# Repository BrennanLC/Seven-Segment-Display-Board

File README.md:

# Seven-Segment-Display-Board
This is a kicad design project for a seven segment display board

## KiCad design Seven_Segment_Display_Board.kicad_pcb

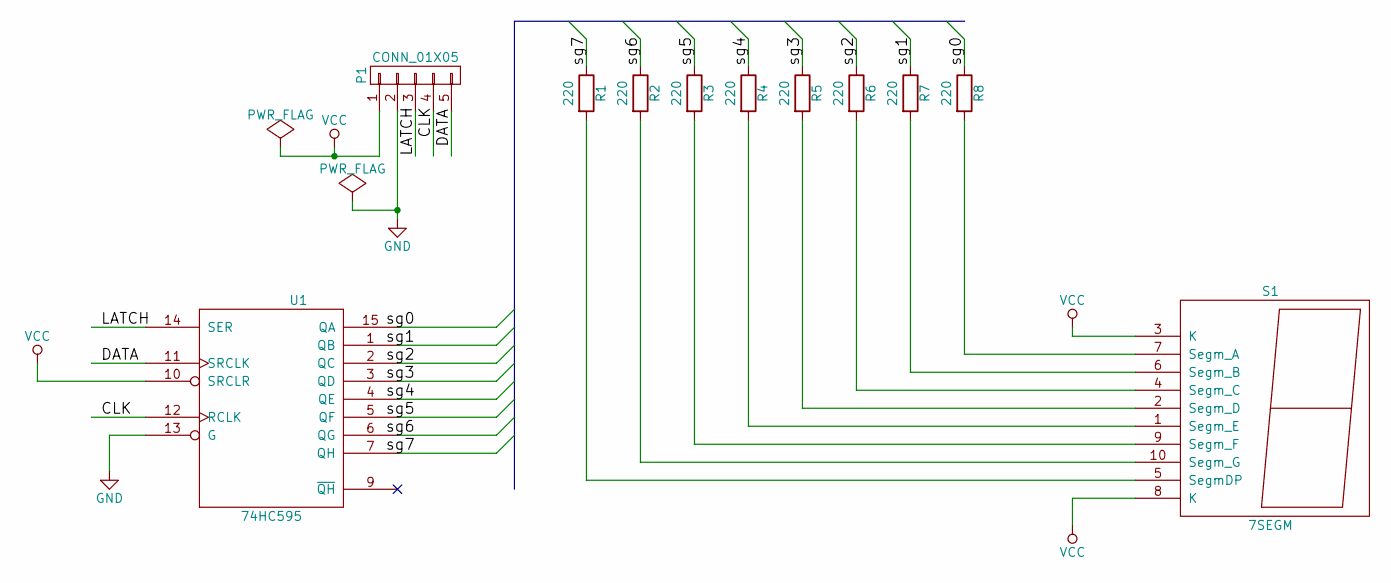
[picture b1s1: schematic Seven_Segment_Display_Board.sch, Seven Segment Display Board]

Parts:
P1: CONN_01X05; Pin_Header_Straight_1x05
R1, R2, R3, R4, R5, R6, R7, R8: 220; Resistor_Horizontal_RM10mm
S1: 7SEGM; 7SegmentLED_LTS6760_LTS6780
U1: 74HC595; DIP-16_W7.62mm

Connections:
/CLK: P1.4, U1.12 (RCLK)
/DATA: P1.5, U1.11 (SRCLK)
/LATCH: P1.3, U1.14 (SER)
/sg0: R8.1, U1.15 (QA)
/sg1: R7.1, U1.1 (QB)
/sg2: R6.1, U1.2 (QC)
/sg3: R5.1, U1.3 (QD)
/sg4: R4.1, U1.4 (QE)
/sg5: R3.1, U1.5 (QF)
/sg6: R2.1, U1.6 (QG)
/sg7: R1.1, U1.7 (QH)
GND: P1.2, U1.8 (GND), U1.13 (G)
unnamed: R1.2, S1.5 (SegmDP)
unnamed: R2.2, S1.10 (Segm_G)
unnamed: R3.2, S1.9 (Segm_F)
unnamed: R4.2, S1.1 (Segm_E)
unnamed: R5.2, S1.2 (Segm_D)
unnamed: R6.2, S1.4 (Segm_C)
unnamed: R7.2, S1.6 (Segm_B)
unnamed: R8.2, S1.7 (Segm_A)
VCC: P1.1, S1.3 (K), S1.8 (K), U1.10 (SRCLR), U1.16 (VCC)

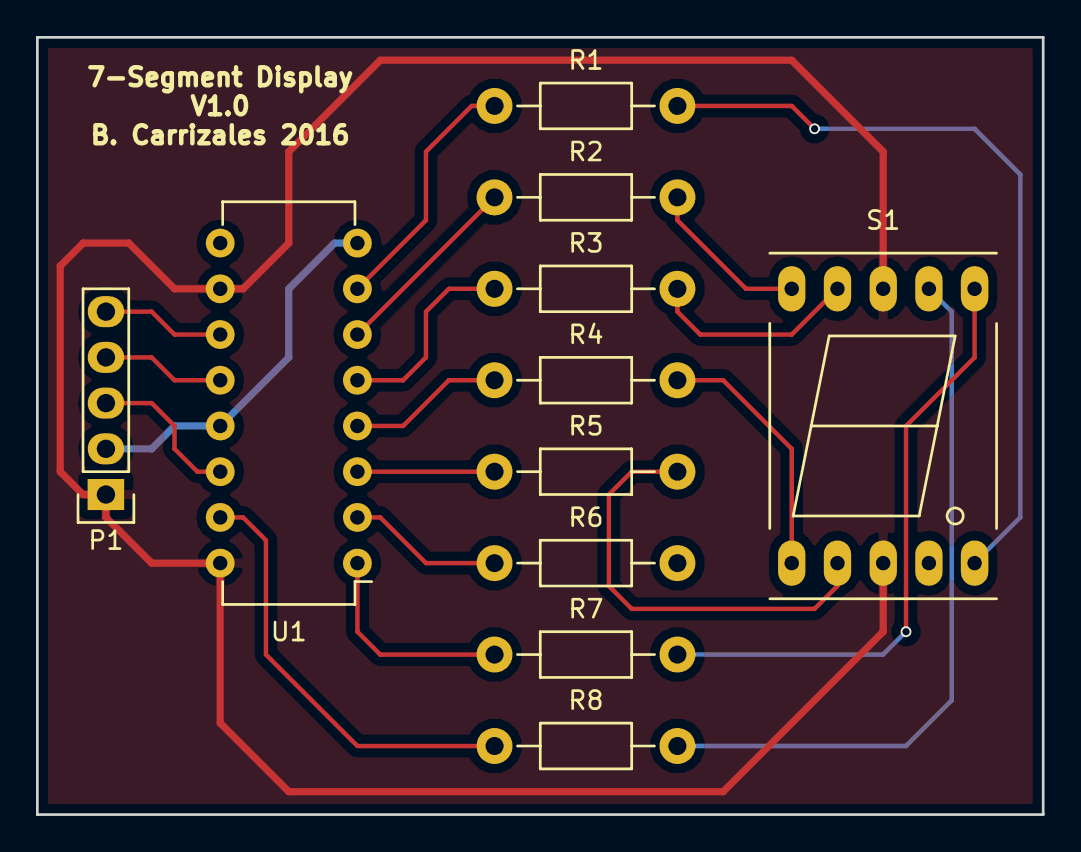
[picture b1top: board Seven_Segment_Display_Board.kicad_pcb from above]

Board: 2 copper layers, 55.9 x 43.2 mm, 11 parts (0 on the bottom side), 21 nets.

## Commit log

2016-09-05 Initial Project Files
    All of the project files for the first version of the board
2016-09-05 Update .gitignore
    removed entries for .net files and .csv and .xml files for BOMs
2016-09-05 Add Netlists to Repository
    added in generated netlist file to the repository.
